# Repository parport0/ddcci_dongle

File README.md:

# ddcci_dongle

An RP2040-powered dongle to be plugged between your computer and the monitor.

Continuation of the thread of thought of [dvi_i2c_checkpoint](https://github.com/parport0/dvi_i2c_checkpoint) + [ddcci_injector](https://github.com/parport0/ddcci_injector).

This dongle should allow you, given a functioning firmware, to inject your DDC/CI sequences into a video cable.

There is an I2C channel broken out into the 3.5mm jack (GND/SDA/SCK/3V3). This should allow a theoretical user to have a control button or similar mounted close to their fingers, without having to pull heavy video cables onto the desk.

* JLC04161H-7628
* Make sure to select "NanYa NP-155F" as the material when ordering to guarantee impedance control
* HDMI connectors are best bought separately and soldered manually to avoid added PCBA costs

# Firmware

The firmware is a simplification of the [ddcci_injector](https://github.com/parport0/ddcci_injector) firmware.

It assumes there is a Sparkfun Qwiic Twist sitting on the other end, connected to a 4-pin audio jack.

This uses:

* [The arduino-pico core of earlephilhower](https://github.com/earlephilhower/arduino-pico)

```
arduino-cli config add board_manager.additional_urls https://github.com/earlephilhower/arduino-pico/releases/download/global/package_rp2040_index.json
arduino-cli core update-index
arduino-cli core install rp2040:rp2040

arduino-cli compile -e -v --fqbn rp2040:rp2040:rpipico ddcci_dongle_sw.ino
```

The build result will be in `build/rp2040.rp2040.rpipico/ddcci_dongle_sw.ino.uf2`

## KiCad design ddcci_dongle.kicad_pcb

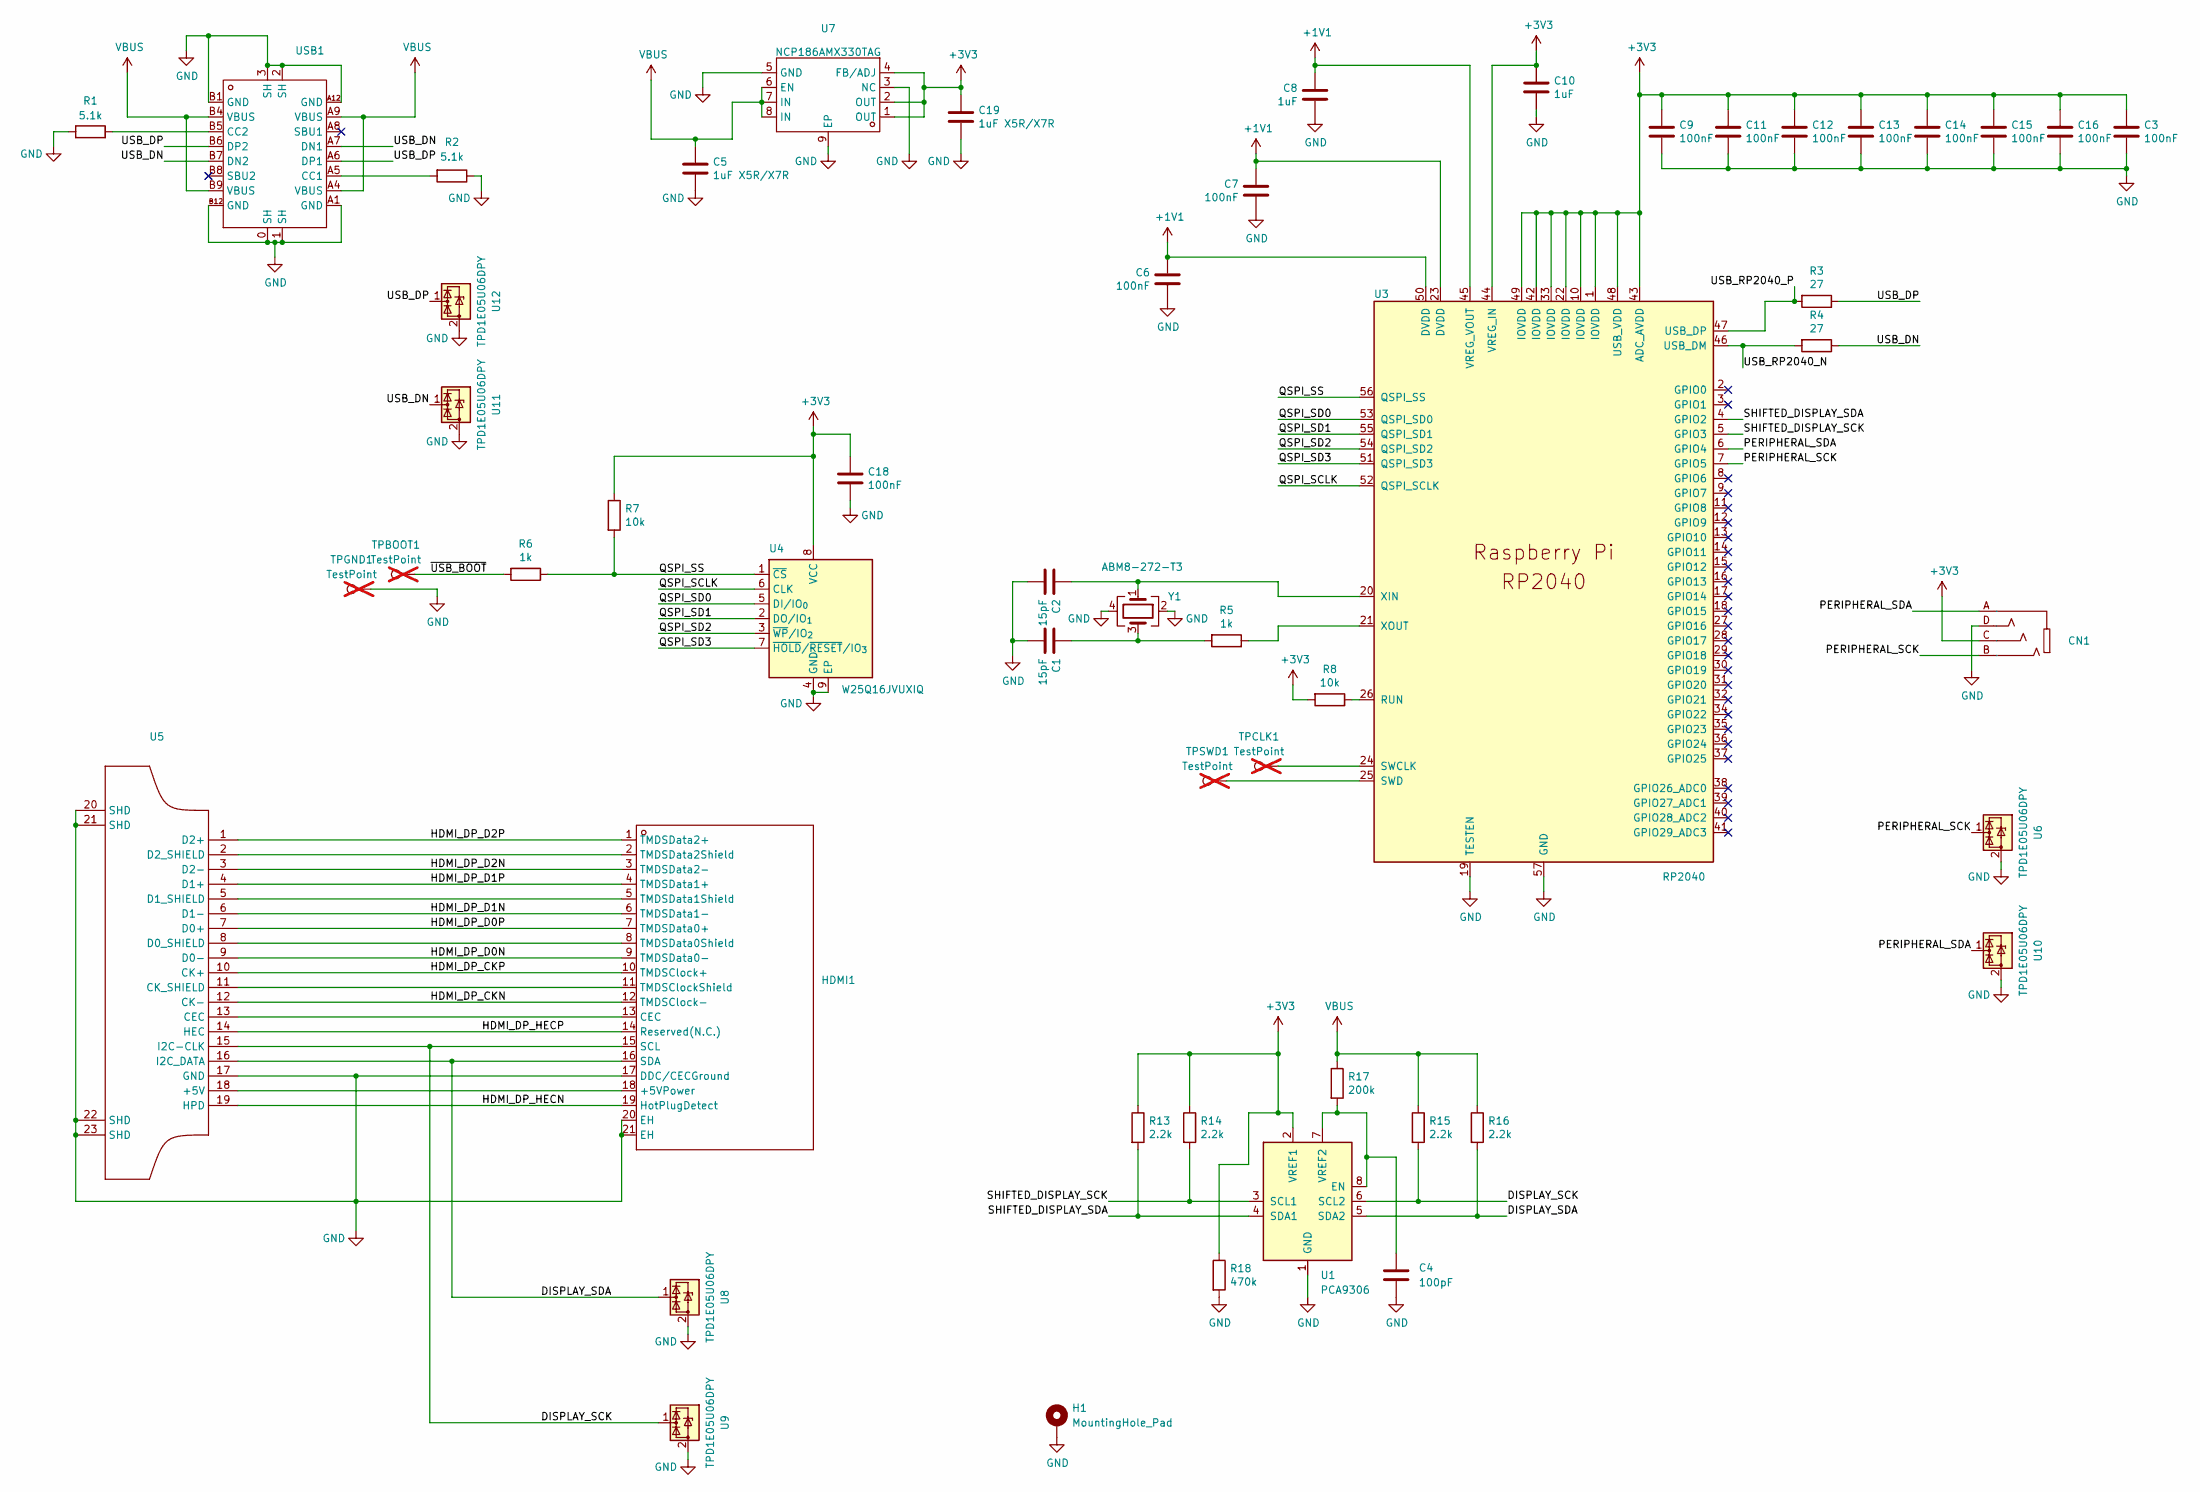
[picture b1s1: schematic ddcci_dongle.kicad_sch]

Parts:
C1, C2: 15pF; C_0402_1005Metric; LCSC Part C1548
C3, C6, C7, C9, C11, C12, C13, C14, C15, C16, C18: 100nF; C_0402_1005Metric; LCSC Part C1525
C4: 100pF; C_0603_1608Metric; LCSC Part C14858
C5, C19: 1uF X5R/X7R; C_0805_2012Metric; LCSC Part C28323
C8, C10: 1uF; C_0402_1005Metric; LCSC Part C52923
CN1: AUDIO-TH_PJ-320A-4P-DIP; Manufacturer Part PJ-320A-4P DIP; LCSC Part Name 3.5mm耳机座
H1: MountingHole_Pad; MountingHole_2.2mm_M2_Pad
HDMI1: HDMI-SMD_KH-HDMI-0021-JBS; LCSC Part Name KH-HDMI-0021-JBS
R1, R2: 5.1k; R_0402_1005Metric; LCSC Part C25905
R3, R4: 27; R_0402_1005Metric; LCSC Part C137890
R5, R6: 1k; R_0402_1005Metric; LCSC Part C11702
R7, R8: 10k; R_0402_1005Metric; LCSC Part C25744
R13, R14, R15, R16: 2.2k; R_0402_1005Metric; LCSC Part C25879
R17: 200k; R_0402_1005Metric; LCSC Part C25764
R18: 470k; R_0603_1608Metric; LCSC Part C23178
TPBOOT1: TestPoint; TestPoint_Pad_D1.5mm; not fitted
TPCLK1: TestPoint; TestPoint_Pad_D1.5mm; not fitted
TPGND1: TestPoint; TestPoint_Pad_D1.5mm; not fitted
TPSWD1: TestPoint; TestPoint_Pad_D1.5mm; not fitted
U1: PCA9306; VSSOP-8_2.3x2mm_P0.5mm; LCSC Part C33196
U3: RP2040; QFN-56-1EP_7x7mm_P0.4mm_EP3.2x3.2mm; LCSC Part C2040
U4: W25Q16JVUXIQ; Winbond_USON-8-1EP_3x2mm_P0.5mm_EP0.2x1.6mm; LCSC Part C2843335
U5: HDMI-SMD_HDMI-GD-136PWB; LCSC Part Name HDMI-A 母 19P
U6, U8, U9, U10, U11, U12: TPD1E05U06DPY; Texas_DPY0002A_0.6x1mm_P0.65mm; LCSC Part C436349
U7: XDFN-8_L1.6-W1.2-P0.40-BL-EP; Manufacturer Part NCP186AMX330TAG; LCSC Part Name NCP186AMX330TAG
USB1: USB-C_SMD-TYPE-C-31-M-12; LCSC Part Name Type-C 母 卧贴
Y1: ABM8-272-T3; Crystal_SMD_3225-4Pin_3.2x2.5mm; LCSC Part C20625731

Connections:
+1V1: C6.1, C7.1, C8.1, U3.23 (DVDD), U3.45 (VREG_VOUT), U3.50 (DVDD)
+3V3: C3.1, C9.1, C10.1, C11.1, C12.1, C13.1, C14.1, C15.1, C16.1, C18.1, C19.1, CN1.C, R7.1, R8.2, R13.1, R14.1, R18.1, U1.2 (VREF1), U3.1 (IOVDD), U3.10 (IOVDD), U3.22 (IOVDD), U3.33 (IOVDD), U3.42 (IOVDD), U3.43 (ADC_AVDD), U3.44 (VREG_IN), U3.48 (USB_VDD), U3.49 (IOVDD), U4.8 (VCC), U7.1 (OUT), U7.2 (OUT), U7.4 (FB/ADJ)
/DISPLAY_SCK: HDMI1.15 (SCL), R15.2, U1.6 (SCL2), U5.15 (I2C-CLK), U9.1 (I/O)
/DISPLAY_SDA: HDMI1.16 (SDA), R16.2, U1.5 (SDA2), U5.16 (I2C_DATA), U8.1 (I/O)
/HDMI_DP_CKN: HDMI1.12 (TMDSClock-), U5.12 (CK-)
/HDMI_DP_CKP: HDMI1.10 (TMDSClock+), U5.10 (CK+)
/HDMI_DP_D0N: HDMI1.9 (TMDSData0-), U5.9 (D0-)
/HDMI_DP_D0P: HDMI1.7 (TMDSData0+), U5.7 (D0+)
/HDMI_DP_D1N: HDMI1.6 (TMDSData1-), U5.6 (D1-)
/HDMI_DP_D1P: HDMI1.4 (TMDSData1+), U5.4 (D1+)
/HDMI_DP_D2N: HDMI1.3 (TMDSData2-), U5.3 (D2-)
/HDMI_DP_D2P: HDMI1.1 (TMDSData2+), U5.1 (D2+)
/HDMI_DP_HECN: HDMI1.19 (HotPlugDetect), U5.19 (HPD)
/HDMI_DP_HECP: HDMI1.14 (Reserved(N.C.)), U5.14 (HEC)
/PERIPHERAL_SCK: CN1.B, U3.7 (GPIO5), U6.1 (I/O)
/PERIPHERAL_SDA: CN1.A, U3.6 (GPIO4), U10.1 (I/O)
/QSPI_SCLK: U3.52 (QSPI_SCLK), U4.6 (CLK)
/QSPI_SD0: U3.53 (QSPI_SD0), U4.5 (DI/IO_{0})
/QSPI_SD1: U3.55 (QSPI_SD1), U4.2 (DO/IO_{1})
/QSPI_SD2: U3.54 (QSPI_SD2), U4.3 (~WP/IO_{2})
/QSPI_SD3: U3.51 (QSPI_SD3), U4.7 (~HOLD/~RESET/IO_{3})
/QSPI_SS: R6.1, R7.2, U3.56 (QSPI_SS), U4.1 (~CS)
/SHIFTED_DISPLAY_SCK: R14.2, U1.3 (SCL1), U3.5 (GPIO3)
/SHIFTED_DISPLAY_SDA: R13.2, U1.4 (SDA1), U3.4 (GPIO2)
/USB_DN: R4.1, U11.1 (I/O), USB1.A7 (DN1), USB1.B7 (DN2)
/USB_DP: R3.1, U12.1 (I/O), USB1.A6 (DP1), USB1.B6 (DP2)
/USB_RP2040_N: R4.2, U3.46 (USB_DM)
/USB_RP2040_P: R3.2, U3.47 (USB_DP)
/~USB_BOOT: R6.2, TPBOOT1.1
GND: C1.2, C2.2, C3.2, C4.2, C5.2, C6.2, C7.2, C8.2, C9.2, C10.2, C11.2, C12.2, C13.2, C14.2, C15.2, C16.2, C18.2, C19.2, CN1.D, H1.1, HDMI1.17 (DDC/CECGround), HDMI1.20 (EH), HDMI1.21 (EH), R1.1, R2.1, R18.2, TPGND1.1, U1.1 (GND), U3.19 (TESTEN), U3.57 (GND), U4.4 (GND), U4.9 (EP), U5.17 (GND), U5.20 (SHD), U5.21 (SHD), U5.22 (SHD), U5.23 (SHD), U6.2 (GND), U7.3 (NC), U7.5 (GND), U7.9 (EP), U8.2 (GND), U9.2 (GND), U10.2 (GND), U11.2 (GND), U12.2 (GND), USB1.0 (SH), USB1.1 (SH), USB1.2 (SH), USB1.3 (SH), USB1.A1 (GND), USB1.A12 (GND), USB1.B1 (GND), USB1.B12 (GND), Y1.2, Y1.4
unnamed: C1.1, R5.2, Y1.3
unnamed: HDMI1.18 (+5VPower), U5.18 (+5V)
unnamed: HDMI1.13 (CEC), U5.13 (CEC)
unnamed: HDMI1.11 (TMDSClockShield), U5.11 (CK_SHIELD)
unnamed: HDMI1.8 (TMDSData0Shield), U5.8 (D0_SHIELD)
unnamed: HDMI1.5 (TMDSData1Shield), U5.5 (D1_SHIELD)
unnamed: HDMI1.2 (TMDSData2Shield), U5.2 (D2_SHIELD)
unnamed: C4.1, R17.2, U1.7 (VREF2), U1.8 (EN)
unnamed: R8.1, U3.26 (RUN)
unnamed: TPCLK1.1, U3.24 (SWCLK)
unnamed: TPSWD1.1, U3.25 (SWD)
unnamed: C2.1, U3.20 (XIN), Y1.1
unnamed: R5.1, U3.21 (XOUT)
unnamed: R2.2, USB1.A5 (CC1)
unnamed: R1.2, USB1.B5 (CC2)
VBUS: C5.1, R15.1, R16.1, R17.1, U7.6 (EN), U7.7 (IN), U7.8 (IN), USB1.A4 (VBUS), USB1.A9 (VBUS), USB1.B4 (VBUS), USB1.B9 (VBUS)

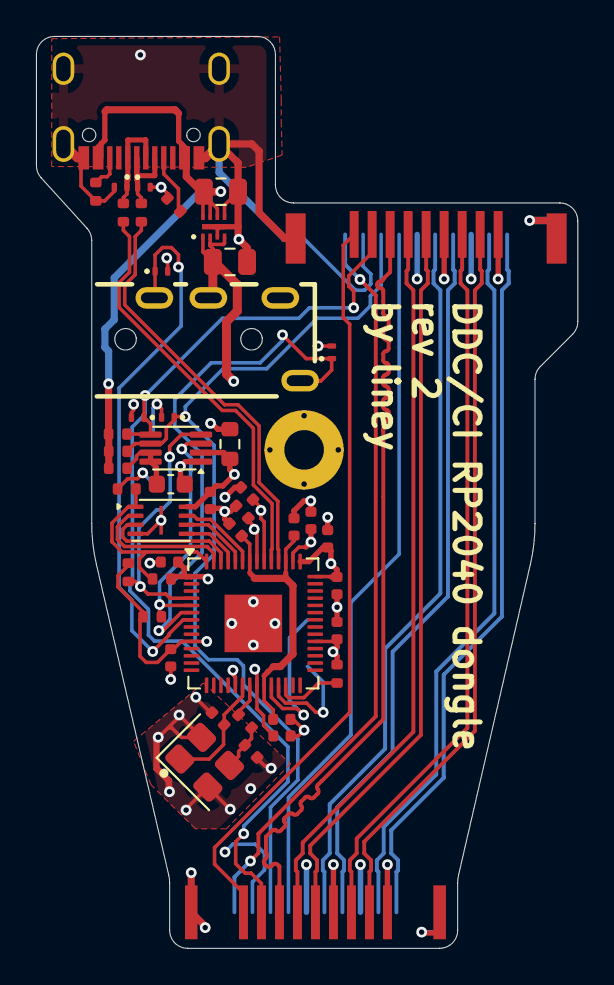
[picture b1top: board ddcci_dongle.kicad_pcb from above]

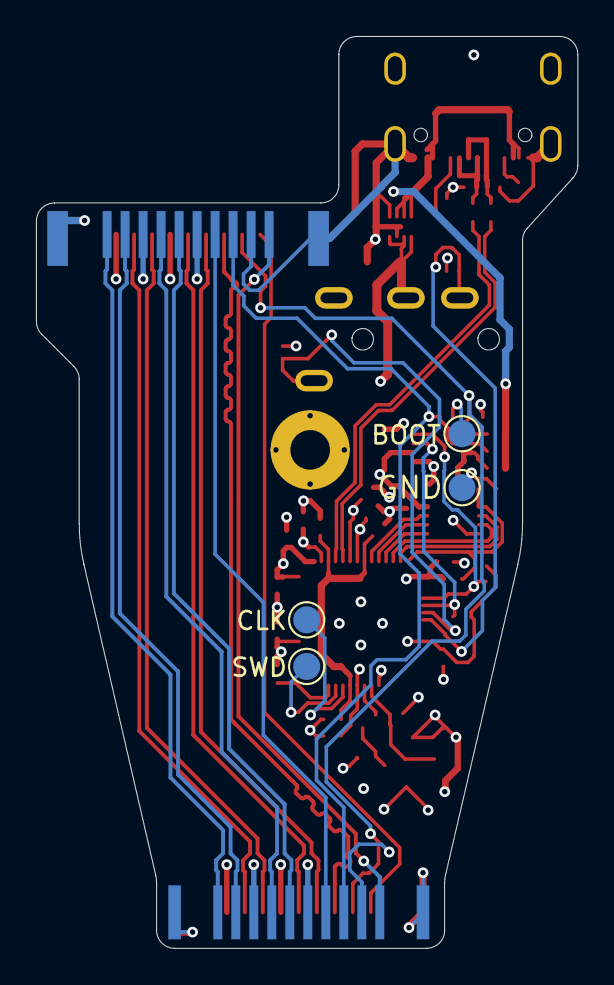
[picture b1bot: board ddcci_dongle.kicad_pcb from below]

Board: 4 copper layers, 30.1 x 50.7 mm, 52 parts (6 on the bottom side), 46 nets.

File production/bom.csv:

Designator,Footprint,Quantity,Value,LCSC Part #
"C1, C2",0402,2,15pF,C1548
"C10, C8",0402,2,1uF,C52923
"C11, C12, C13, C14, C15, C16, C18, C3, C6, C7, C9",0402,11,100nF,C1525
"C19, C5",0805,2,1uF X5R/X7R,C28323
C4,0603,1,100pF,C14858
CN1,AUDIO-TH_PJ-320A-4P-DIP,1,~,C431535
HDMI1,HDMI-SMD_KH-HDMI-0021-JBS,1,~,C5204144
"R1, R2",0402,2,5.1k,C25905
"R13, R14, R15, R16",0402,4,2.2k,C25879
R17,0402,1,200k,C25764
R18,0603,1,470k,C23178
"R3, R4",0402,2,27,C137890
"R5, R6",0402,2,1k,C11702
"R7, R8",0402,2,10k,C25744
U1,VSSOP-8_2.3x2mm_P0.5mm,1,PCA9306,C33196
"U10, U11, U12, U6, U8, U9",Texas_DPY0002A_0.6x1mm_P0.65mm,6,TPD1E05U06DPY,C436349
U3,QFN-56-1EP_7x7mm_P0.4mm_EP3.2x3.2mm,1,RP2040,C2040
U4,Winbond_USON-8-1EP_3x2mm_P0.5mm_EP0.2x1.6mm,1,W25Q16JVUXIQ,C2843335
U5,HDMI-SMD_HDMI-GD-136PWB,1,~,C7425346
U7,XDFN-8_L1.6-W1.2-P0.40-BL-EP,1,~,
USB1,USB-C_SMD-TYPE-C-31-M-12,1,~,C2927038
Y1,Crystal_SMD_3225-4Pin_3.2x2.5mm,1,ABM8-272-T3,C20625731

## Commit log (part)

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2026-02-23 Initial import
2026-02-23 Add a schematics pdf
2026-03-01 Final update before rev1 production
    * Update LCSC PN# fields
    * Add ground to layer 3 (3.3v has been reduced to a polygon)
    * Remove the antennas on the right (behind HDMI lanes)
    * Remove the ground plane "capacitor" under the XTAL
    * Prettier testpoint labels
    * Prettier tracks overall
2026-03-17 Fix SDA/SCL for the monitor. Bump to rev2
2026-03-23 WIP: Make the board narrower
    Todo: make the board shorter
2026-04-03 Make the board shorter for rev2
2026-04-05 Follow serpentine recommendations
    > When a serpentine section is used to match one length to another, ...
    > the length of each jog must be at least three times the trace width.
    > The maximum distance between traces in a serpentine section should be less
    > than two times the distance between traces in a non-serpentine section.
2026-04-10 Make the board even shorter
2026-04-10 Change pinout of the TRRS jack
    This way the board won't burn if a TRS cable is plugged in.
